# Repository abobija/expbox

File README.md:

# PCB Exposure Box [expbox]

This is repository of PCB Exposure Box [expbox] which uses PIC16F886 for it's brain and shows the time on display made up out of four seven-segment led modules.

Because display is made up out of 4 digits, I have decided to limit **maximum exposure time**, that can be set, to **1 hour** (**59m59s**). Even 1 hour is more than enough, because exposure process takes no more than maximum 10 to 15 minutes.

After the countdown comes to zero, finish of exposure process will be signalized with 1 second of high frequency tone.

### Demo

## Microcontroller

Microcontroller used in this project is [**PIC16F886**](https://www.microchip.com/wwwproducts/en/PIC16F886) produced by [Microchip](https://www.microchip.com) company. This MCU has three timers and each timer is assigned to a separated task. **Timer0** is responsible for multiplexing four seven-segment led modules. **Timer1** is shared between tasks for precise time measuring and buttons debouncing. And last, but not least, **Timer2** is in charge of driving piezo speaker with **P**ulse **W**ide **M**odulated signal.

The controller uses an **internal oscillator** and it's set to maximum frequency of **8 MHz**.

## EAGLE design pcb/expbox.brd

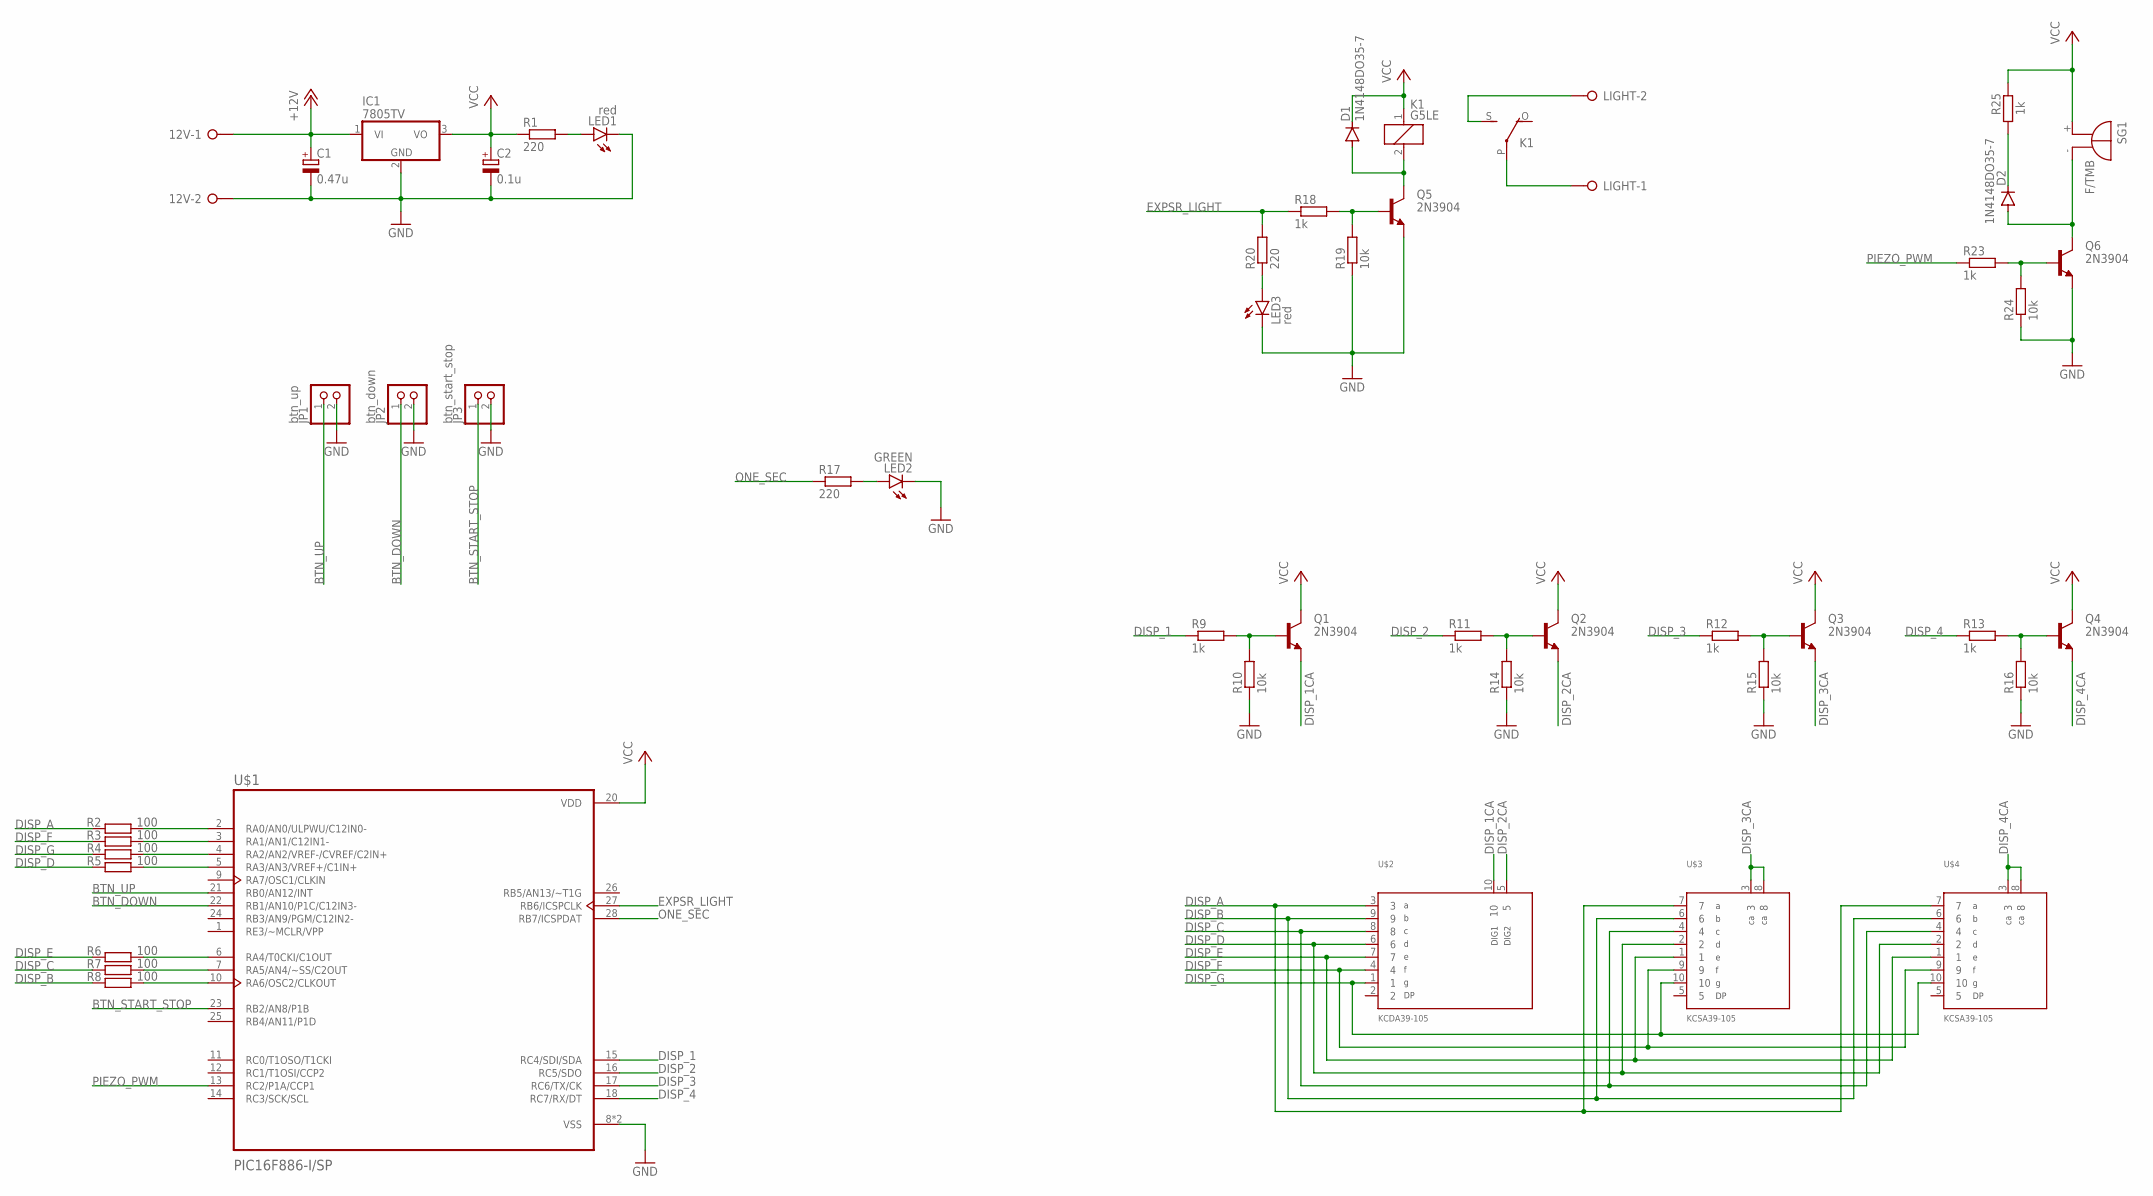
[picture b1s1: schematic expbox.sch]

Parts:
12V: W237-02P; W237-132
C1: 0.47u; E2,5-5
C2: 0.1u; E2-4
D1, D2: 1N4148DO35-7; DO35-7
IC1: 7805TV; TO220V
JP1: btn_up; 1X02
JP2: btn_down; 1X02
JP3: btn_start_stop; 1X02
K1: G5LE
LED1, LED3: red; LED3MM
LED2: GREEN; 1206
LIGHT: W237-02P; W237-132
Q1, Q2, Q3, Q4, Q5, Q6: 2N3904; SOT23-BEC
R1, R17, R20: 220; R0805
R2, R3, R4, R5, R6, R7, R8: 100; M1206
R9, R11, R12, R13, R18, R23, R25: 1k; R0805
R10, R14, R15, R16, R19, R24: 10k; R0805
SG1: F/TMB
U$1: PIC16F886-I/SP; DIP762W46P254L3467H457Q28
U$2: KCDA39-105
U$3, U$4: KCSA39-105

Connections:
+12V: 12V.1, C1.+, IC1.1 (VI)
BTN_DOWN: JP2.1, U$1.22 (RB1/AN10/P1C/C12IN3-)
BTN_START_STOP: JP3.1, U$1.23 (RB2/AN8/P1B)
BTN_UP: JP1.1, U$1.21 (RB0/AN12/INT)
DISP_1: R9.1, U$1.15 (RC4/SDI/SDA)
DISP_1CA: Q1.E, U$2.10
DISP_2: R11.1, U$1.16 (RC5/SDO)
DISP_2CA: Q2.E, U$2.5
DISP_3: R12.1, U$1.17 (RC6/TX/CK)
DISP_3CA: Q3.E, U$3.3, U$3.8
DISP_4: R13.1, U$1.18 (RC7/RX/DT)
DISP_4CA: Q4.E, U$4.3, U$4.8
DISP_A: R2.1, U$2.3, U$3.7, U$4.7
DISP_B: R8.1, U$2.9, U$3.6, U$4.6
DISP_C: R7.1, U$2.8, U$3.4, U$4.4
DISP_D: R5.1, U$2.6, U$3.2, U$4.2
DISP_E: R6.1, U$2.7, U$3.1, U$4.1
DISP_F: R3.1, U$2.4, U$3.9, U$4.9
DISP_G: R4.1, U$2.1, U$3.10, U$4.10
EXPSR_LIGHT: R18.1, R20.2, U$1.27 (RB6/ICSPCLK)
GND: 12V.2, C1.-, C2.-, IC1.2 (GND), JP1.2, JP2.2, JP3.2, LED1.K (C), LED2.C, LED3.K (C), Q5.E, Q6.E, R10.1, R14.1, R15.1, R16.1, R19.1, R24.1, U$1.8 (VSS), U$1.19 (VSS)
unnamed: LED1.A, R1.2
unnamed: R2.2, U$1.2 (RA0/AN0/ULPWU/C12IN0-)
unnamed: R3.2, U$1.3 (RA1/AN1/C12IN1-)
unnamed: R4.2, U$1.4 (RA2/AN2/VREF-/CVREF/C2IN+)
unnamed: R5.2, U$1.5 (RA3/AN3/VREF+/C1IN+)
unnamed: R6.2, U$1.6 (RA4/T0CKI/C1OUT)
unnamed: R7.2, U$1.7 (RA5/AN4/~SS/C2OUT)
unnamed: R8.2, U$1.10 (RA6/OSC2/CLKOUT)
unnamed: Q2.B, R11.2, R14.2
unnamed: Q1.B, R9.2, R10.2
unnamed: Q3.B, R12.2, R15.2
unnamed: Q4.B, R13.2, R16.2
unnamed: LED2.A, R17.2
unnamed: K1.S, LIGHT.2
unnamed: Q5.B, R18.2, R19.2
unnamed: D1.A, K1.2, Q5.C
unnamed: K1.P, LIGHT.1
unnamed: LED3.A, R20.1
unnamed: D2.A, Q6.C, SG1.-
unnamed: Q6.B, R23.2, R24.2
unnamed: D2.C, R25.1
ONE_SEC: R17.1, U$1.28 (RB7/ICSPDAT)
PIEZO_PWM: R23.1, U$1.13 (RC2/P1A/CCP1)
VCC: C2.+, D1.C, IC1.3 (VO), K1.1, Q1.C, Q2.C, Q3.C, Q4.C, R1.1, R25.2, SG1.+, U$1.20 (VDD)

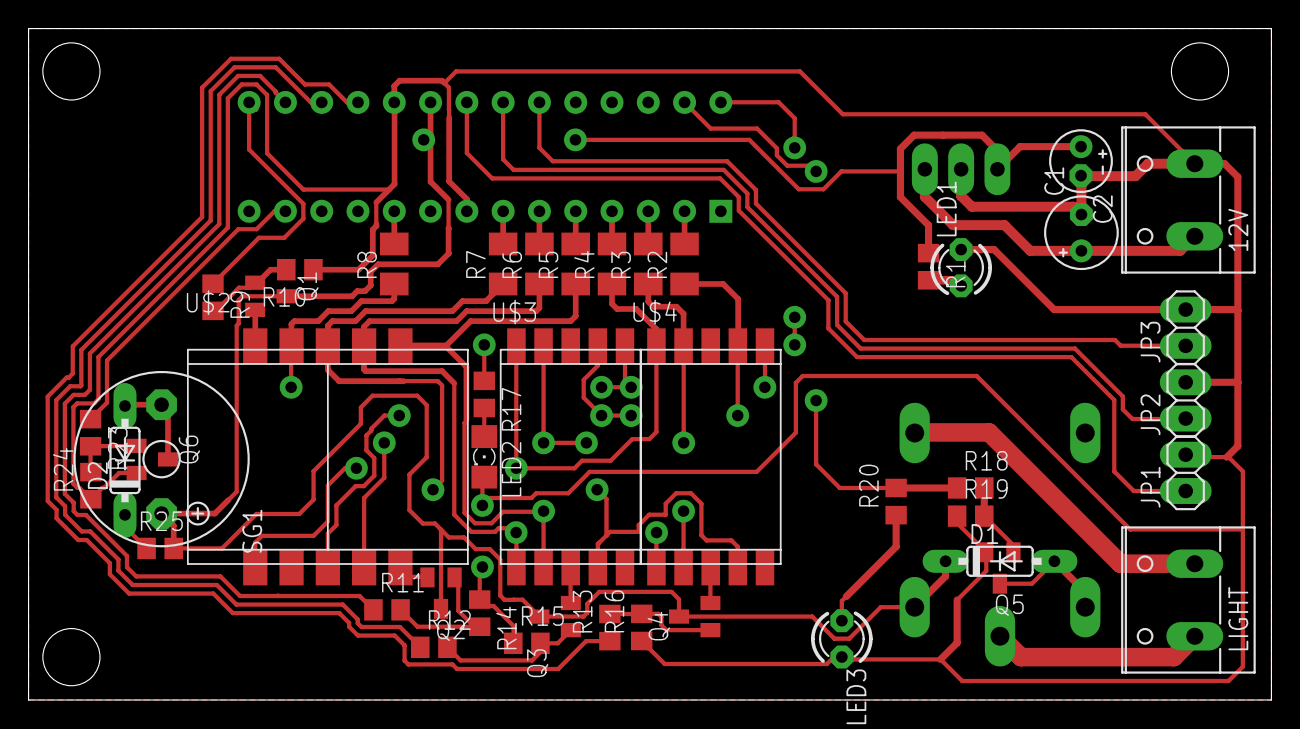
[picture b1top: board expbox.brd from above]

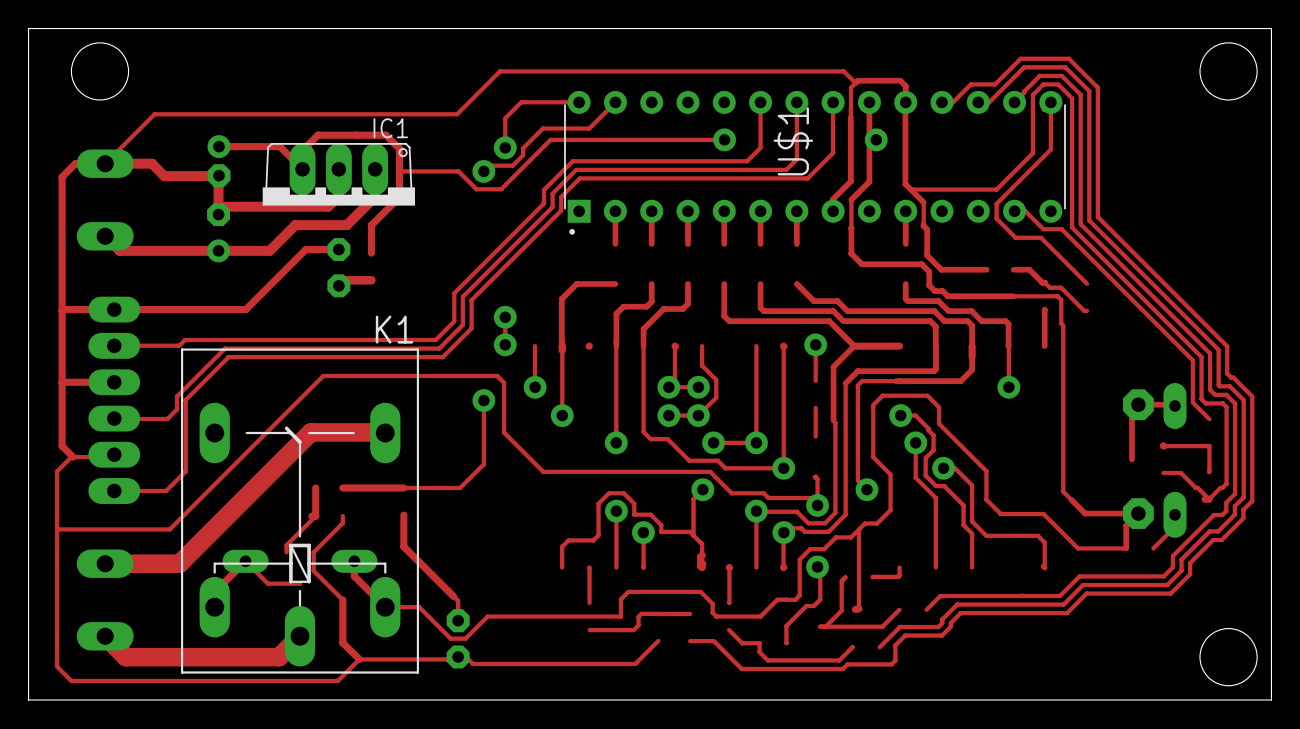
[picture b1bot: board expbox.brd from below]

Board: 2 copper layers, 87.0 x 47.0 mm, 48 parts (3 on the bottom side), 45 nets.

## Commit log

2020-10-05 Initial firmware commit
2020-10-05 Used typedef instead of define for uint8_t and uint16_t. Calculate one second tick out of __FOSC__ predefined project constant
2020-10-05 Typedefs and definitions moved to defs.h
    Separated files for display module
    Multiplexing (rate has been fine tuned by experimental way)
2020-10-05 Updated project file
2020-10-05 Headers moved to /include
2020-10-06 Display moved to port C
2020-10-06 Enable interrupt-on-change and weak pull-ups on port B
2020-10-06 Revert int-on-change during constatly entering in interrupt
2020-10-06 Make display timer interrupt handler function more generic
2020-10-06 One second counter moved to Timer1 and display multiplexing stays on Timer0
2020-10-06 Refactored. Added disp_init() and called in main(). disp_interrupt_handler() foo changed to be inline foo
2020-10-07 Timer source files and corresponding foos for init and interrupt handler
2020-10-07 Buttons source files initial commit
2020-10-07 Introduced tmr_one_sec_callback
2020-10-07 Display mux rate assigned directly to Tmr0 prescaler
2020-10-07 Configured Tmr2 for buttons
2020-10-07 Set internal osc freq according to predefined constant __FOSC__
    Set prescalers and all project timings according to __FOSC__
    Supported project freqs are 8, 4 and 2 [MHz]
    If unsupported frequency are choosen, preprocessor error will be risen
2020-10-07 buttons_scan renamed to buttons_read
2020-10-07 Change buttons timer(2) prescaler from 1:16 to 1:4
2020-10-07 Implemented buttons debouncing algorithm
2020-10-07 Declare main foos in main header
2020-10-07 Introducted xtime. Local xtime var attached to display. Increment/Decrement time handlers assign to corresponding buttons
2020-10-07 Clean cmd
2020-10-08 Buttons burst mode implemented
    Freq raised from 4 to 8MHz bcs display flicker at 4MHz while button is in burst mode
2020-10-08 Countdown mechanism. Disable up/down buttons while countdown.
2020-10-08 Return to origin time when countdown is done
2020-10-08 Exposure light on/off
2020-10-08 Refactoring
2020-10-08 Move display to port A<0:7> and port C<4:7>
2020-10-08 Enable weak pull-ups
2020-10-08 Play 1sec of sound on piezo when countdown is finish
2020-10-08 Only 8MHz oscillator is supported
2020-10-09 Save/Read time from EEPROM
2020-10-09 Optimized display. Remask display port only when mux flag is raised
2020-10-10 Save time to EEPROM only when time is actually changed
2020-10-10 Update README. Intro and MCU sections
2020-10-11 Buttons debouncing moved to Timer1 (which is shared now with countdown)
2020-10-11 Piezo source files
2020-10-11 Typo fix
2020-10-12 PCB Eagle files
2020-10-13 Replace buzzer with one with wider legs
2020-10-14 Remask display port for common anode smd 7 seg displays
2020-10-14 Fixed display mask
2020-10-14 Turn off display by set all pins to high
2020-10-15 Sketchup 3d model
2020-10-17 Update README - added yt demo
